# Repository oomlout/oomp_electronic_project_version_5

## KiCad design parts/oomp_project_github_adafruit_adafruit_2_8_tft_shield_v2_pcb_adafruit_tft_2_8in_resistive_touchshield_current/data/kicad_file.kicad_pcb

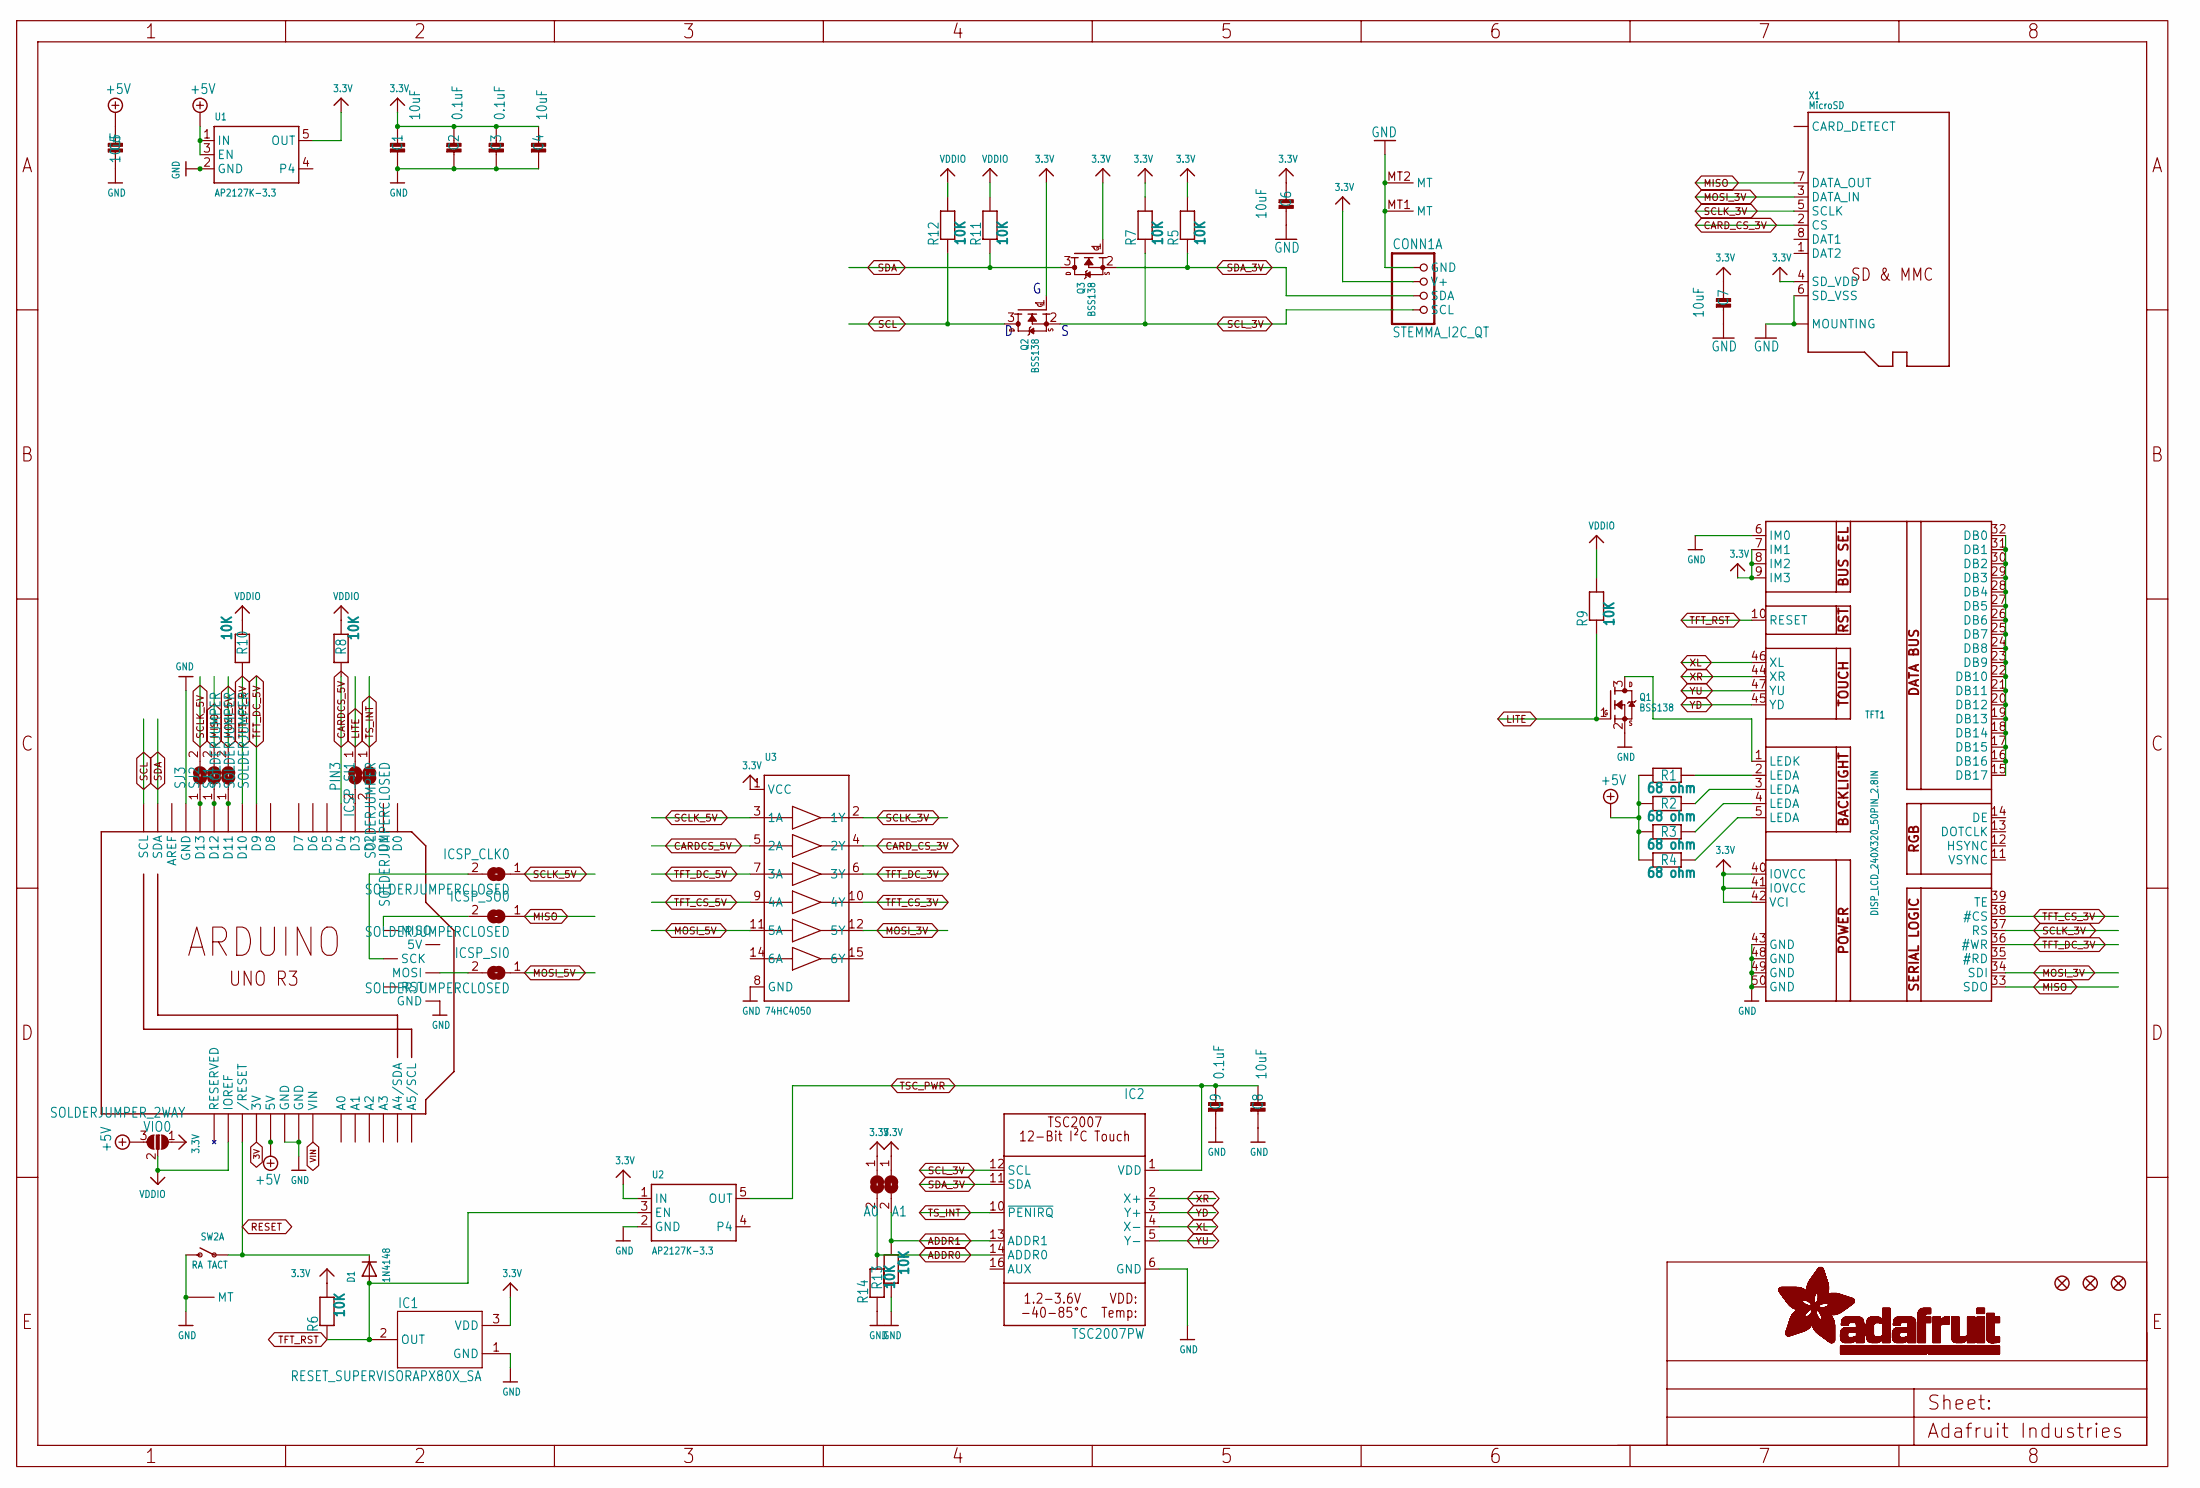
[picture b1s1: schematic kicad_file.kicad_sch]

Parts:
ARD0: ARDUINO_R3_ICSPSMT; ARDUINOR3_ICSP_SMT
C1, C4, C5, C6, C7, C8: 10uF; 0805-NO
C2, C3, C9: 0.1uF; 0603-NO
CONN1: STEMMA_I2C_QT; JST_SH4; LCSC C2845363
D1: 1N4148; SOD-323F
IC1: RESET_SUPERVISORAPX80X_SA; SOT23-WIDE
IC2: TSC2007PW; TSSOP16
ICSP_CLK0: SOLDERJUMPERCLOSED; SOLDERJUMPER_CLOSEDWIRE
ICSP_CLK1: A1; SOLDERJUMPER_ARROW_NOPASTE
ICSP_CLK2: A0; SOLDERJUMPER_ARROW_NOPASTE
ICSP_SI0, ICSP_SI1: SOLDERJUMPERCLOSED; SOLDERJUMPER_CLOSEDWIRE
ICSP_SO0: SOLDERJUMPERCLOSED; SOLDERJUMPER_CLOSEDWIRE
PIN3: SOLDERJUMPER; SOLDERJUMPER_ARROW_NOPASTE
Q1, Q2, Q3: BSS138; SOT23-WIDE
R1, R2, R3, R4: 68 ohm; 0603-NO
R5, R6, R7, R8, R9, R10, R11, R12, R13, R14: 10K; 0603-NO
SJ1, SJ2, SJ3: SOLDERJUMPER; SOLDERJUMPER_ARROW_NOPASTE
SW2: RA TACT; SPST_TACTILE_RA; LCSC C778159
TFT1: DISP_LCD_240X320_50PIN_2.8IN; TFT_2.83IN_240X320_50PIN
U1, U2: AP2127K-3.3; SOT23-5; JLC_ROTATION 270
U3: 74HC4050; SOIC16
U$10, U$11, U$19: FIDUCIAL_1MM
VIO0: SOLDERJUMPER_2WAY; SOLDERJUMPER_2WAY_OPEN_NOPASTE
X1: MicroSD; MICROSD; JLC_ROTATION 90

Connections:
3.3V: C1.1, C2.1, C3.1, C4.1, C6.1, C7.1, CONN1.2 (V+), IC1.3 (VDD), ICSP_CLK1.1, ICSP_CLK2.1, Q2.1 (G), Q3.1 (G), R5.2, R6.2, R7.2, TFT1.7 (IM1), TFT1.8 (IM2), TFT1.9 (IM3), TFT1.40 (IOVCC), TFT1.41 (IOVCC), TFT1.42 (VCI), U1.5 (OUT), U2.1 (IN), U3.1 (VCC), VIO0.1, X1.4 (SD_VDD)
3V: ARD0.3V
+5V: ARD0.5V, C5.1, R1.1, R2.1, R3.1, R4.1, U1.1 (IN), U1.3 (EN), VIO0.3
ADDR0: IC2.14 (ADDR0), ICSP_CLK2.2, R14.2
ADDR1: IC2.13 (ADDR1), ICSP_CLK1.2, R13.2
BACKLITE: ARD0.D3, PIN3.2
CARDCS_5V: ARD0.D4, R8.1, U3.5 (2A)
CARD_CS_3V: U3.4 (2Y), X1.2 (CS)
GND: ARD0.GND, ARD0.GND@1 (GND), ARD0.GND@2 (GND), ARD0.GND@3 (GND), C1.2, C2.2, C3.2, C4.2, C5.2, C6.2, C7.2, C8.2, C9.2, CONN1.1 (GND), CONN1.MT1 (MT), CONN1.MT2 (MT), IC1.1 (GND), IC2.6 (GND), Q1.2 (S), R13.1, R14.1, SW2.2 (S), SW2.MT1 (MT), SW2.MT2 (MT), TFT1.6 (IM0), TFT1.43 (GND), TFT1.48 (GND), TFT1.49 (GND), TFT1.50 (GND), U1.2 (GND), U2.2 (GND), U3.8 (GND), X1.6 (SD_VSS), X1.MT1 (MOUNTING), X1.MT2 (MOUNTING)
LITE: PIN3.1, Q1.1 (G), R9.1
MISO: ICSP_SO0.1, SJ2.2, TFT1.33 (SDO), X1.7 (DATA_OUT)
MOSI_3V: TFT1.34 (SDI), U3.12 (5Y), X1.3 (DATA_IN)
MOSI_5V: ICSP_SI0.1, SJ1.2, U3.11 (5A)
unnamed: Q1.3 (D), TFT1.1 (LEDK)
unnamed: R1.2, TFT1.2 (LEDA)
unnamed: R2.2, TFT1.3 (LEDA)
unnamed: R3.2, TFT1.4 (LEDA)
unnamed: ARD0.MOSI, ICSP_SI0.2
unnamed: ARD0.D2, ICSP_SI1.2
unnamed: TFT1.15 (DB17), TFT1.16 (DB16), TFT1.17 (DB15), TFT1.18 (DB14), TFT1.19 (DB13), TFT1.20 (DB12), TFT1.21 (DB11), TFT1.22 (DB10), TFT1.23 (DB9), TFT1.24 (DB8), TFT1.25 (DB7), TFT1.26 (DB6), TFT1.27 (DB5), TFT1.28 (DB4), TFT1.29 (DB3), TFT1.30 (DB2), TFT1.31 (DB1), TFT1.32 (DB0)
unnamed: R4.2, TFT1.5 (LEDA)
unnamed: ARD0.MISO, ICSP_SO0.2
unnamed: ARD0.SCK, ICSP_CLK0.2
unnamed: ARD0.D13, SJ3.1
unnamed: ARD0.D12, SJ2.1
unnamed: ARD0.D11, SJ1.1
RESET: ARD0.RESET (/RESET), D1.C, SW2.1
SCL: ARD0.SCL, Q2.3 (D), R12.1
SCLK_3V: TFT1.37 (RS), U3.2 (1Y), X1.5 (SCLK)
SCLK_5V: ICSP_CLK0.1, SJ3.2, U3.3 (1A)
SCL_3V: CONN1.4 (SCL), IC2.12 (SCL), Q2.2 (S), R7.1
SDA: ARD0.SDA, Q3.3 (D), R11.1
SDA_3V: CONN1.3 (SDA), IC2.11 (SDA), Q3.2 (S), R5.1
TFT_CS_3V: TFT1.38 (#CS), U3.10 (4Y)
TFT_CS_5V: ARD0.D10, R10.1, U3.9 (4A)
TFT_DC_3V: TFT1.36 (#WR), U3.6 (3Y)
TFT_DC_5V: ARD0.D9, U3.7 (3A)
TFT_RST: D1.A, IC1.2 (OUT), R6.1, TFT1.10 (RESET), U2.3 (EN)
TSC_PWR: C8.1, C9.1, IC2.1 (VDD), U2.5 (OUT)
TS_INT: IC2.10 (~PENIRQ), ICSP_SI1.1
VDDIO: ARD0.IOREF, R8.2, R9.2, R10.2, R11.2, R12.2, VIO0.2
VIN: ARD0.VIN
XL: IC2.4 (X-), TFT1.46 (XL)
XR: IC2.2 (X+), TFT1.44 (XR)
YD: IC2.3 (Y+), TFT1.45 (YD)
YU: IC2.5 (Y-), TFT1.47 (YU)

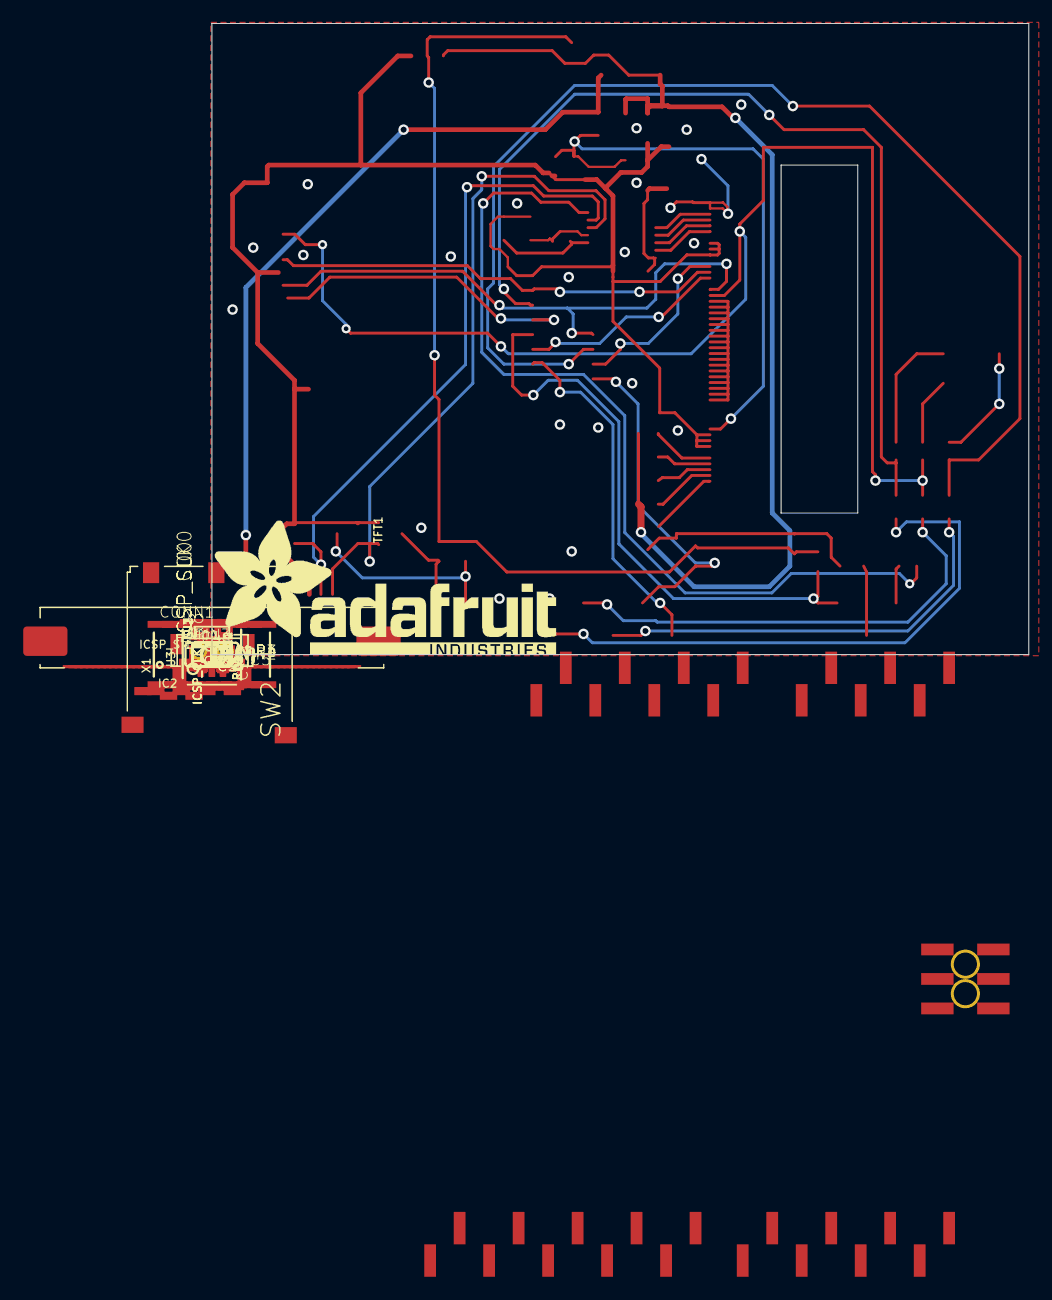
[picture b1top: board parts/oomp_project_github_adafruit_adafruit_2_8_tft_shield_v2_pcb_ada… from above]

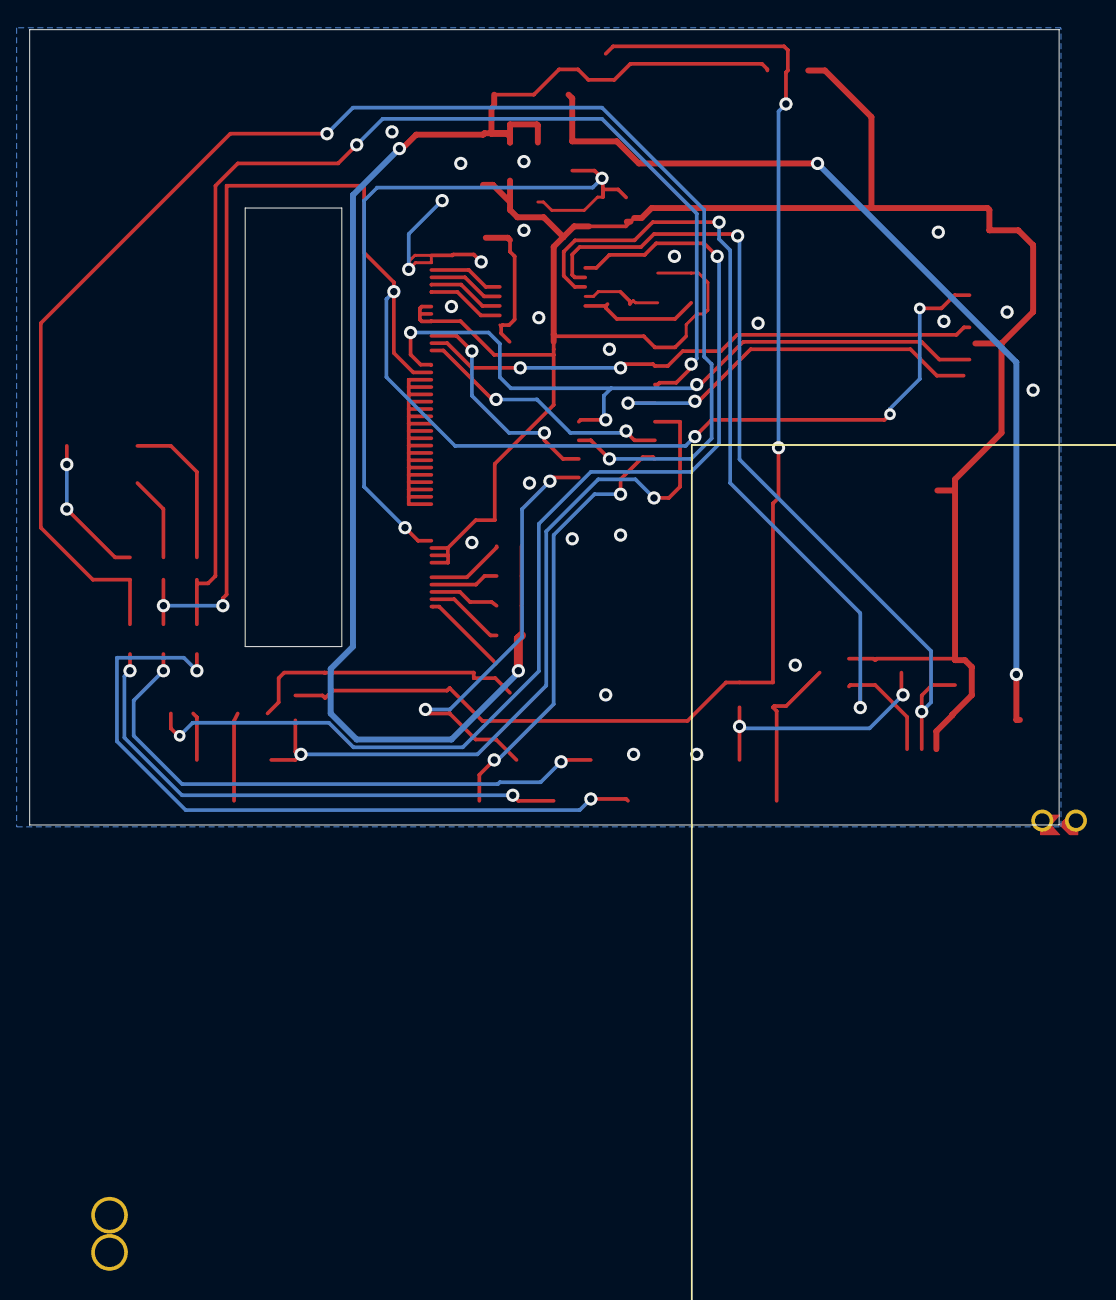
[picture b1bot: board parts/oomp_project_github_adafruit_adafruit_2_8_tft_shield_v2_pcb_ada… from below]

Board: 16 copper layers, 70.4 x 54.4 mm, 76 parts (2 on the bottom side), 44 nets.

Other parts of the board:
PLABEL0: PLABEL0
PLABEL1: PLABEL1
PLABEL2: PLABEL2
PLABEL3: PLABEL3
PLABEL4: PLABEL4
PLABEL5: PLABEL5
PLABEL6: PLABEL6
PLABEL7: PLABEL7
PLABEL8: PLABEL8
PLABEL9: PLABEL9
PLABEL10: PLABEL10
PLABEL11: PLABEL11
PLABEL12: PLABEL12
PLABEL13: PLABEL13
PLABEL14: PLABEL14
PLABEL15: PLABEL15
PLABEL16: PLABEL16
PLABEL17: PLABEL17
PLABEL18: PLABEL18
PLABEL19: PLABEL19
PLABEL20: PLABEL20
PLABEL21: PLABEL21
PLABEL22: PLABEL22
U$3: PCBFEAT-REV-040
U$20: ADAFRUIT_TEXT_30MM

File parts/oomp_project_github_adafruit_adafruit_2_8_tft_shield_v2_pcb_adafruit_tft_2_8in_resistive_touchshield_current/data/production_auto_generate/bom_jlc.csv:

Comment,Designator,Footprint,LCSC Part #
,U$20,Adafruit TFT 2.8in Resistive Touchshield rev E-import-fps:ADAFRUIT_TEXT_30MM,
,U$3,Adafruit TFT 2.8in Resistive Touchshield rev E-import-fps:PCBFEAT-REV-040,
,PLABEL0,Adafruit TFT 2.8in Resistive Touchshield rev E-import-fps:PLABEL0,
,PLABEL1,Adafruit TFT 2.8in Resistive Touchshield rev E-import-fps:PLABEL1,
,PLABEL10,Adafruit TFT 2.8in Resistive Touchshield rev E-import-fps:PLABEL10,
,PLABEL11,Adafruit TFT 2.8in Resistive Touchshield rev E-import-fps:PLABEL11,
,PLABEL12,Adafruit TFT 2.8in Resistive Touchshield rev E-import-fps:PLABEL12,
,PLABEL13,Adafruit TFT 2.8in Resistive Touchshield rev E-import-fps:PLABEL13,
,PLABEL14,Adafruit TFT 2.8in Resistive Touchshield rev E-import-fps:PLABEL14,
,PLABEL15,Adafruit TFT 2.8in Resistive Touchshield rev E-import-fps:PLABEL15,
,PLABEL16,Adafruit TFT 2.8in Resistive Touchshield rev E-import-fps:PLABEL16,
,PLABEL17,Adafruit TFT 2.8in Resistive Touchshield rev E-import-fps:PLABEL17,
,PLABEL18,Adafruit TFT 2.8in Resistive Touchshield rev E-import-fps:PLABEL18,
,PLABEL19,Adafruit TFT 2.8in Resistive Touchshield rev E-import-fps:PLABEL19,
,PLABEL2,Adafruit TFT 2.8in Resistive Touchshield rev E-import-fps:PLABEL2,
,PLABEL20,Adafruit TFT 2.8in Resistive Touchshield rev E-import-fps:PLABEL20,
,PLABEL21,Adafruit TFT 2.8in Resistive Touchshield rev E-import-fps:PLABEL21,
,PLABEL22,Adafruit TFT 2.8in Resistive Touchshield rev E-import-fps:PLABEL22,
,PLABEL3,Adafruit TFT 2.8in Resistive Touchshield rev E-import-fps:PLABEL3,
,PLABEL4,Adafruit TFT 2.8in Resistive Touchshield rev E-import-fps:PLABEL4,
,PLABEL5,Adafruit TFT 2.8in Resistive Touchshield rev E-import-fps:PLABEL5,
,PLABEL6,Adafruit TFT 2.8in Resistive Touchshield rev E-import-fps:PLABEL6,
,PLABEL7,Adafruit TFT 2.8in Resistive Touchshield rev E-import-fps:PLABEL7,
,PLABEL8,Adafruit TFT 2.8in Resistive Touchshield rev E-import-fps:PLABEL8,
,PLABEL9,Adafruit TFT 2.8in Resistive Touchshield rev E-import-fps:PLABEL9,
,VIO0,Adafruit TFT 2.8in Resistive Touchshield rev E-import-fps:SOLDERJUMPER_2WAY_OPEN_NOPASTE,
,PIN3,Adafruit TFT 2.8in Resistive Touchshield rev E-import-fps:SOLDERJUMPER_ARROW_NOPASTE,
,"ICSP_CLK0,ICSP_SI0,ICSP_SI1,ICSP_SO0",Adafruit TFT 2.8in Resistive Touchshield rev E-import-fps:SOLDERJUMPER_CLOSEDWIRE,
0.1uF,"C2,C3,C9",Adafruit TFT 2.8in Resistive Touchshield rev E-import-fps:0603-NO,C14663
10K,"R5,R6,R7,R8,R9,R10,R11,R12,R13,R14",Adafruit TFT 2.8in Resistive Touchshield rev E-import-fps:0603-NO,C98220
10uF,"C1,C4,C5,C6,C7,C8",Adafruit TFT 2.8in Resistive Touchshield rev E-import-fps:0805-NO,
1N4148,D1,Adafruit TFT 2.8in Resistive Touchshield rev E-import-fps:SOD-323F,
68 ohm,"R1,R2,R3,R4",Adafruit TFT 2.8in Resistive Touchshield rev E-import-fps:0603-NO,C27592
74HC4050,U3,Adafruit TFT 2.8in Resistive Touchshield rev E-import-fps:SOIC16,
A0,ICSP_CLK2,Adafruit TFT 2.8in Resistive Touchshield rev E-import-fps:SOLDERJUMPER_ARROW_NOPASTE,
A1,ICSP_CLK1,Adafruit TFT 2.8in Resistive Touchshield rev E-import-fps:SOLDERJUMPER_ARROW_NOPASTE,
AP2127K-3.3,"U1,U2",Adafruit TFT 2.8in Resistive Touchshield rev E-import-fps:SOT23-5,
ARDUINO_R3_ICSPSMT,ARD0,Adafruit TFT 2.8in Resistive Touchshield rev E-import-fps:ARDUINOR3_ICSP_SMT,
BSS138,"Q1,Q2,Q3",Adafruit TFT 2.8in Resistive Touchshield rev E-import-fps:SOT23-WIDE,C52895
DISP_LCD_240X320_50PIN_2.8IN,TFT1,Adafruit TFT 2.8in Resistive Touchshield rev E-import-fps:TFT_2.83IN_240X320_50PIN,
FIDUCIAL_1MM,"U$10,U$11,U$19",Adafruit TFT 2.8in Resistive Touchshield rev E-import-fps:FIDUCIAL_1MM,
MicroSD,X1,Adafruit TFT 2.8in Resistive Touchshield rev E-import-fps:MICROSD,
RA TACT,SW2,Adafruit TFT 2.8in Resistive Touchshield rev E-import-fps:SPST_TACTILE_RA,
RESET_SUPERVISORAPX80X_SA,IC1,Adafruit TFT 2.8in Resistive Touchshield rev E-import-fps:SOT23-WIDE,
STEMMA_I2C_QT,CONN1,Adafruit TFT 2.8in Resistive Touchshield rev E-import-fps:JST_SH4,C160404
TSC2007PW,IC2,Adafruit TFT 2.8in Resistive Touchshield rev E-import-fps:TSSOP16,

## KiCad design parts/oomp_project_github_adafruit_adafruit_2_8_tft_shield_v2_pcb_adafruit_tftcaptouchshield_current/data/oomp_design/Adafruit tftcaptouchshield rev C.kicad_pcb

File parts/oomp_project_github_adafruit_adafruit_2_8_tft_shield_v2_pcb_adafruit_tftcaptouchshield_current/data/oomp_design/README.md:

# OOMP KiCad design copy

Open `Adafruit tftcaptouchshield rev C.kicad_pro` (or the `.kicad_pcb` / `.kicad_sch`) in KiCad. Local OOMP libraries are under `libraries/`. Original inputs are preserved in [../original/](../original/).

Only verified unchanged installed KiCad defaults were renamed. Modified, custom, unmatched and unavailable items remain unchanged. Soldering variants are never swapped during conversion. Existing pad coordinates, nets and UUIDs are preserved.

See [conversion_report.yaml](conversion_report.yaml) for every conversion and skip. Copy this directory before editing; regeneration refuses to overwrite edited design files.

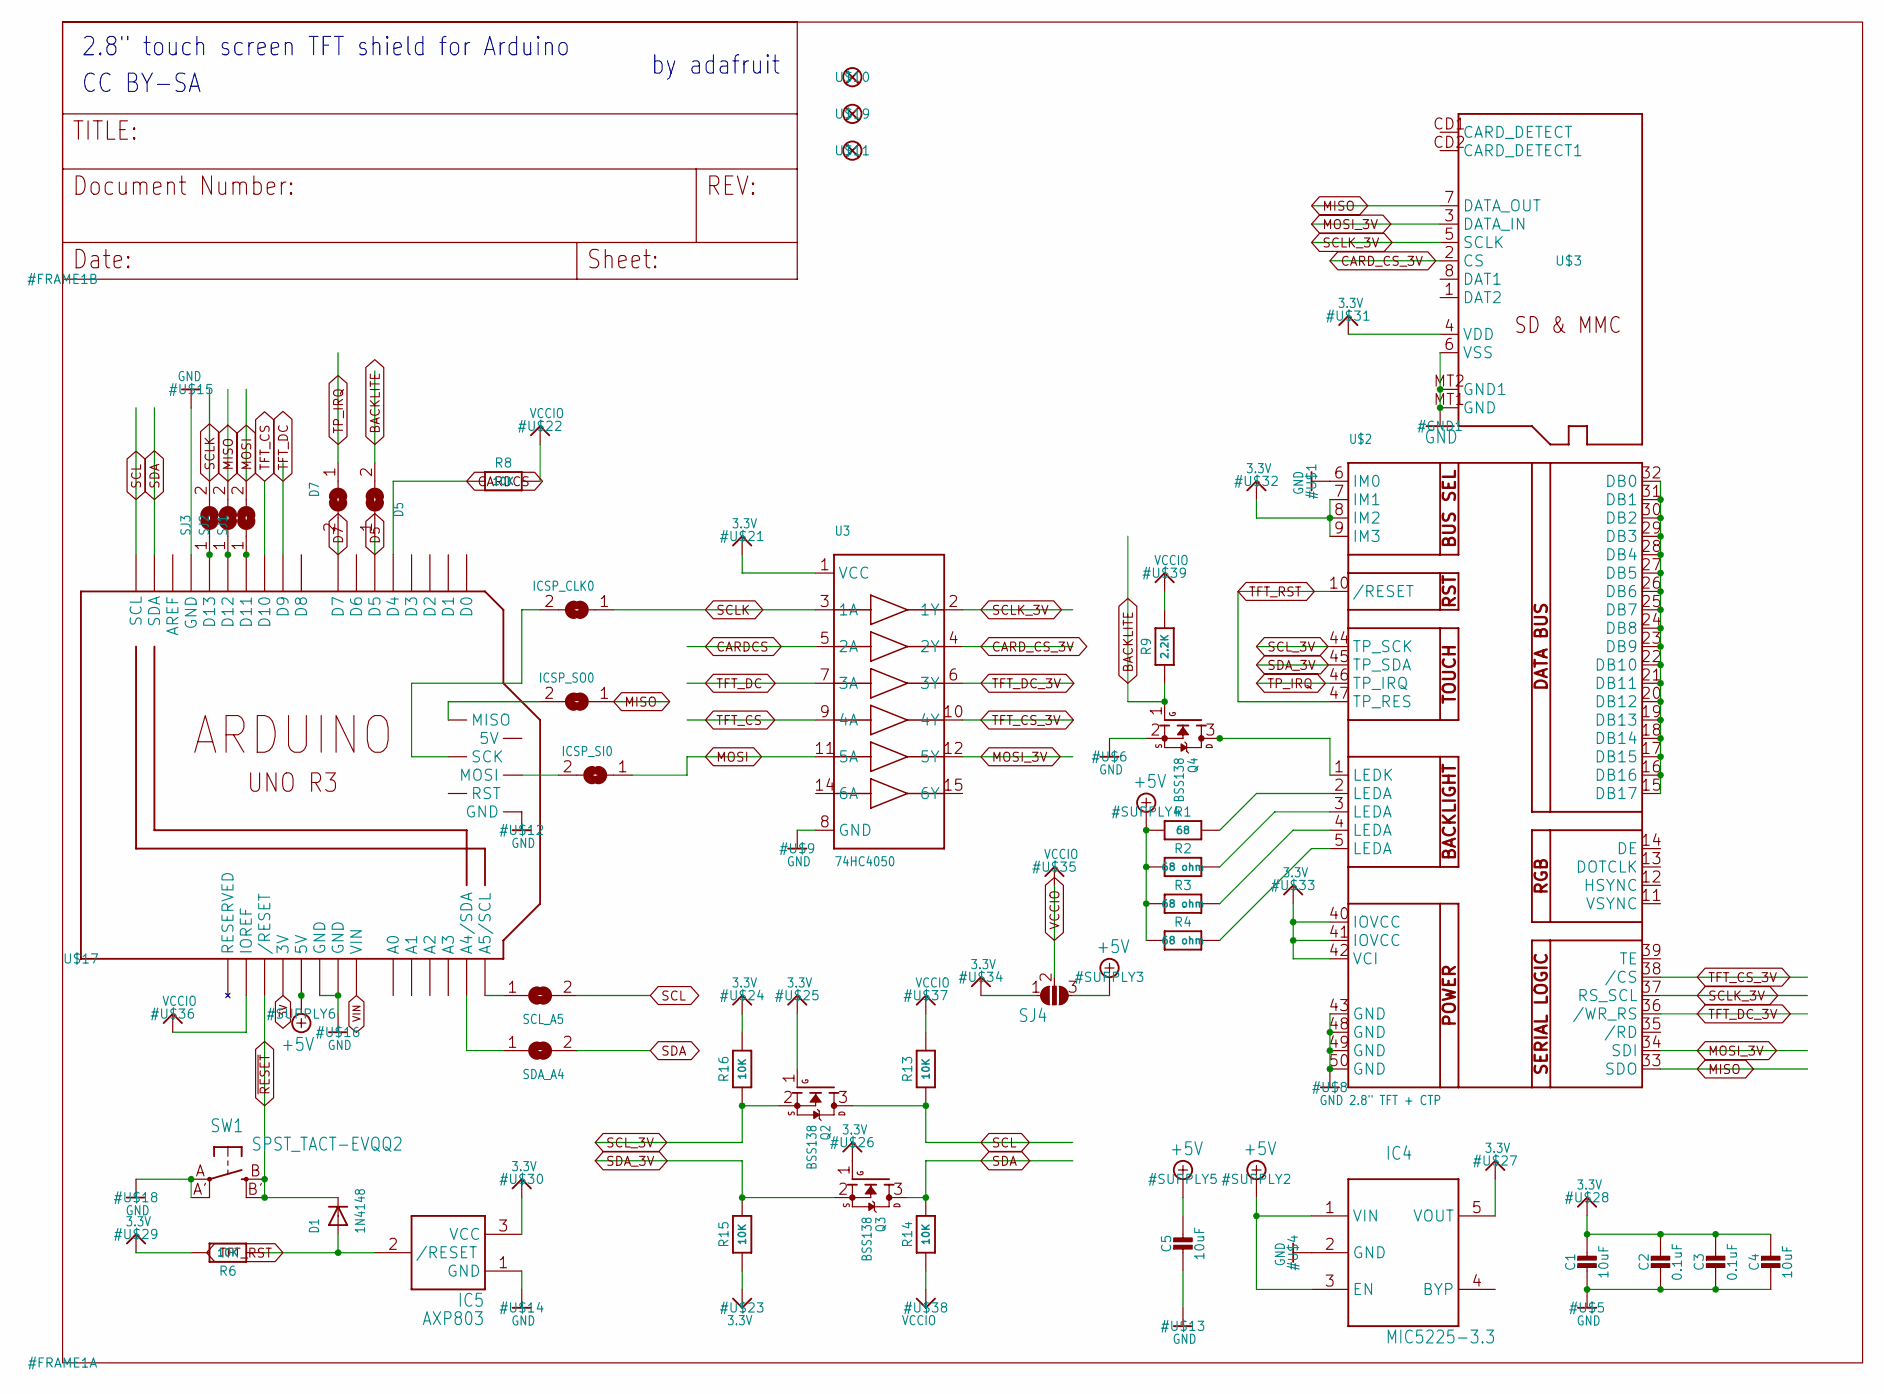
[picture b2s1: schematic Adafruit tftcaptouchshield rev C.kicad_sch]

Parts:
C1, C4, C5: 10uF; 0805-NO
C2, C3: 0.1uF; 0805-NO
D1: 1N4148; SOD-323F
D5, D7: SOLDERJUMPER; SOLDERJUMPER_ARROW_NOPASTE
IC4: MIC5225-3.3; SOT23-5L
IC5: AXP803; SOT23
ICSP_CLK0: SOLDERJUMPERCLOSED; SOLDERJUMPER_CLOSEDWIRE
ICSP_SI0: SOLDERJUMPERCLOSED; SOLDERJUMPER_CLOSEDWIRE
ICSP_SO0: SOLDERJUMPERCLOSED; SOLDERJUMPER_CLOSEDWIRE
Q2, Q3, Q4: BSS138; SOT23-WIDE
R1: 68; 0805-NO
R2, R3, R4: 68 ohm; 0805-NO
R6, R8, R13, R14, R15, R16: 10K; 0805-NO
R9: 2.2K; 0805-NO
SCL_A5: SOLDERJUMPERREFLOW_NOPASTE; SOLDERJUMPER_REFLOW_NOPASTE
SDA_A4: SOLDERJUMPERREFLOW_NOPASTE; SOLDERJUMPER_REFLOW_NOPASTE
SJ1, SJ2, SJ3: SOLDERJUMPER; SOLDERJUMPER_ARROW_NOPASTE
SJ4: SOLDERJUMPER_2WAY; SOLDERJUMPER_2WAY_OPEN_NOPASTE
SW1: SPST_TACT-EVQQ2; EVQ-Q2
U3: 74HC4050; SOIC16
U$2: 2.8" TFT + CTP; TFT_2.83IN_240X320_50PIN
U$3: MICROSD
U$10, U$11, U$19: FIDUCIAL_1MM
U$17: ARDUINO_R3_ICSPSMT; ARDUINOR3_ICSP_SMT

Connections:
3.3V: C1.1, C2.1, C3.1, C4.1, IC4.5 (VOUT), IC5.3 (VCC), Q2.1 (G), Q3.1 (G), R6.2, R15.1, R16.2, SJ4.1, U3.1 (VCC), U$2.7 (IM1), U$2.8 (IM2), U$2.9 (IM3), U$2.40 (IOVCC), U$2.41 (IOVCC), U$2.42 (VCI), U$3.4 (VDD)
3V: U$17.3V
+5V: C5.1, IC4.1 (VIN), IC4.3 (EN), R1.1, R2.1, R3.1, R4.1, SJ4.3, U$17.5V
BACKLITE: D5.2, Q4.1 (G), R9.1
CARDCS: R8.1, U3.5 (2A), U$17.D4
CARD_CS_3V: U3.4 (2Y), U$3.2 (CS)
D5: D5.1, U$17.D5
D7: D7.2, U$17.D7
GND: C1.2, C2.2, C3.2, C4.2, C5.2, IC4.2 (GND), IC5.1 (GND), Q4.2 (S), SW1.A, SW1.A' (P1), U3.8 (GND), U$2.6 (IM0), U$2.43 (GND), U$2.48 (GND), U$2.49 (GND), U$2.50 (GND), U$3.6 (VSS), U$3.MT1 (GND), U$3.MT2 (GND1), U$17.GND, U$17.GND@1 (GND), U$17.GND@2 (GND), U$17.GND@3 (GND)
MISO: ICSP_SO0.1, SJ2.2, U$2.33 (SDO), U$3.7 (DATA_OUT)
MOSI: ICSP_SI0.1, SJ1.2, U3.11 (5A)
MOSI_3V: U3.12 (5Y), U$2.34 (SDI), U$3.3 (DATA_IN)
unnamed: Q4.3 (D), U$2.1 (LEDK)
unnamed: R1.2, U$2.2 (LEDA)
unnamed: R2.2, U$2.3 (LEDA)
unnamed: R3.2, U$2.4 (LEDA)
unnamed: ICSP_SI0.2, U$17.MOSI
unnamed: U$2.15 (DB17), U$2.16 (DB16), U$2.17 (DB15), U$2.18 (DB14), U$2.19 (DB13), U$2.20 (DB12), U$2.21 (DB11), U$2.22 (DB10), U$2.23 (DB9), U$2.24 (DB8), U$2.25 (DB7), U$2.26 (DB6), U$2.27 (DB5), U$2.28 (DB4), U$2.29 (DB3), U$2.30 (DB2), U$2.31 (DB1), U$2.32 (DB0)
unnamed: R4.2, U$2.5 (LEDA)
unnamed: ICSP_SO0.2, U$17.MISO
unnamed: ICSP_CLK0.2, U$17.SCK
unnamed: SJ3.1, U$17.D13
unnamed: SJ2.1, U$17.D12
unnamed: SJ1.1, U$17.D11
unnamed: SDA_A4.1, U$17.A4 (A4/SDA)
unnamed: SCL_A5.1, U$17.A5 (A5/SCL)
SCL: Q2.3 (D), R13.1, SCL_A5.2, U$17.SCL
SCLK: ICSP_CLK0.1, SJ3.2, U3.3 (1A)
SCLK_3V: U3.2 (1Y), U$2.37 (RS_SCL), U$3.5 (SCLK)
SCL_3V: Q2.2 (S), R16.1, U$2.44 (TP_SCK)
SDA: Q3.3 (D), R14.2, SDA_A4.2, U$17.SDA
SDA_3V: Q3.2 (S), R15.2, U$2.45 (TP_SDA)
TFT_CS: U3.9 (4A), U$17.D10
TFT_CS_3V: U3.10 (4Y), U$2.38 (/CS)
TFT_DC: U3.7 (3A), U$17.D9
TFT_DC_3V: U3.6 (3Y), U$2.36 (/WR_RS)
TFT_RST: D1.A, IC5.2 (/RESET), R6.1, U$2.10 (/RESET), U$2.47 (TP_RES)
TP_IRQ: D7.1, U$2.46 (TP_IRQ)
VCCIO: R8.2, R9.2, R13.2, R14.1, SJ4.2, U$17.IOREF
VIN: U$17.VIN
~RESET: D1.C, SW1.B (S), SW1.B' (S1), U$17.RESET (/RESET)

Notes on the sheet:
by adafruit~{}
CC BY-SA
2.8" touch screen TFT shield for Arduino

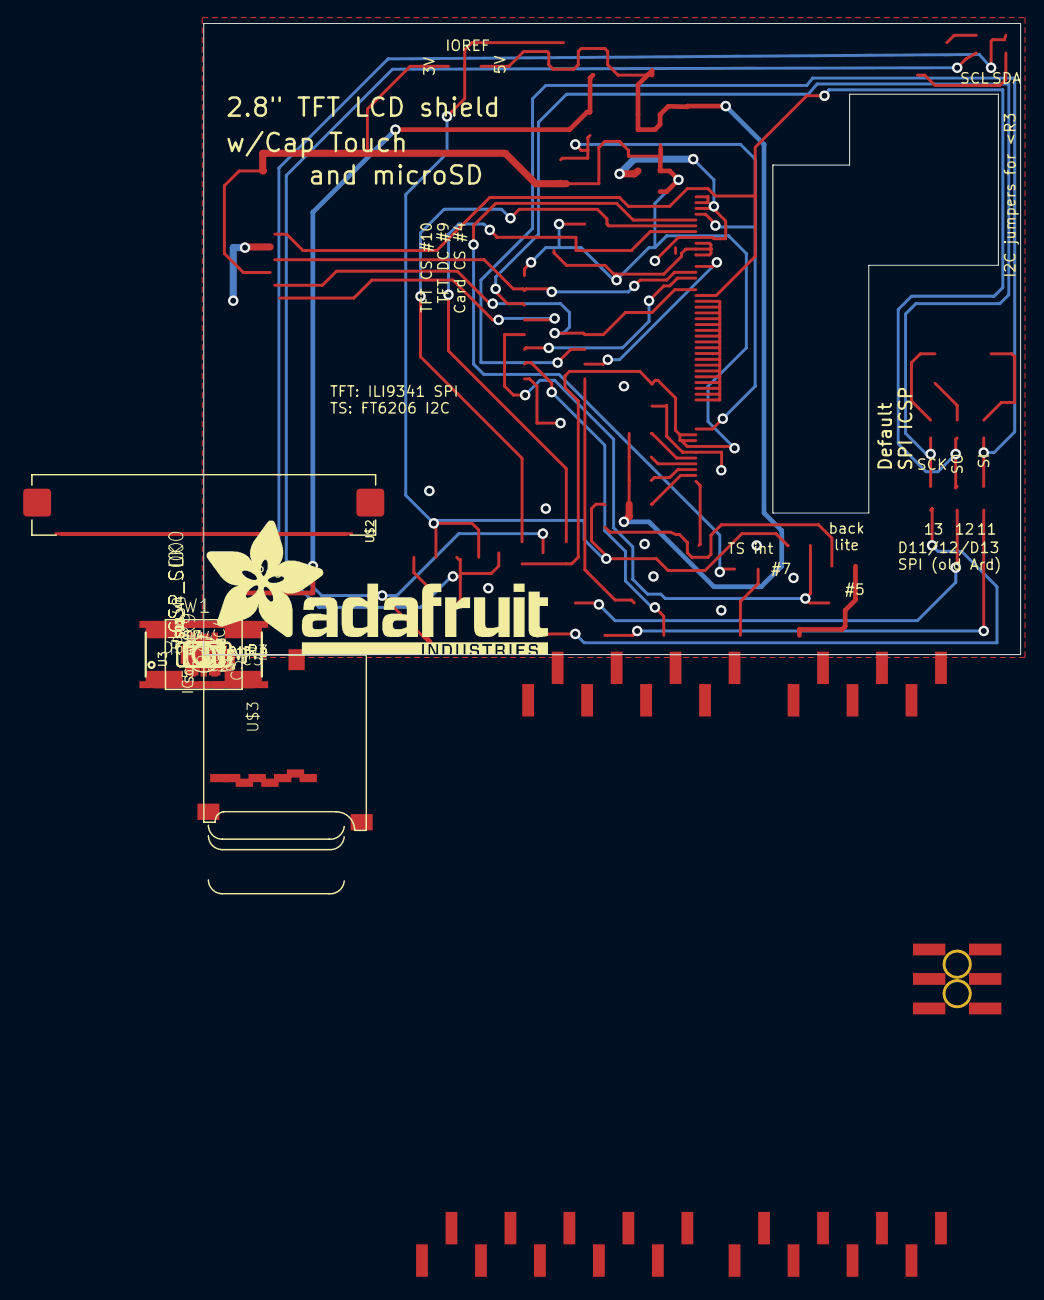
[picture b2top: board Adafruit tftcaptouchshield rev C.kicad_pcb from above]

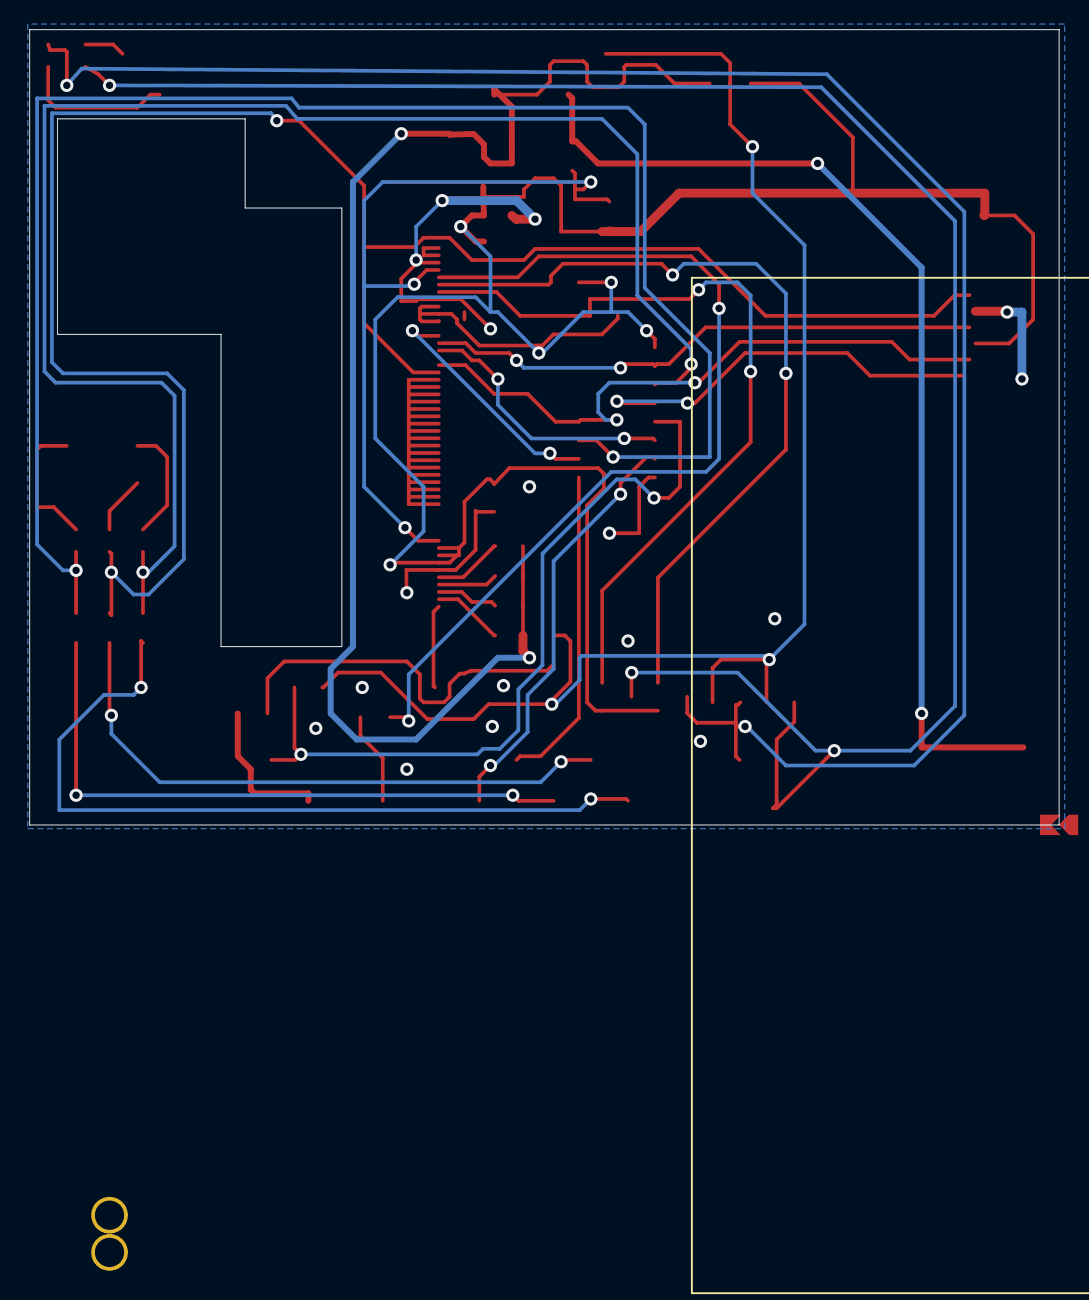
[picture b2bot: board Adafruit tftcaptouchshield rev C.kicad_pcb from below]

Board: 16 copper layers, 70.4 x 54.4 mm, 43 parts (2 on the bottom side), 39 nets.

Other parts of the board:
U$7: PCBFEAT-REV-040
U$20: ADAFRUIT_TEXT_30MM

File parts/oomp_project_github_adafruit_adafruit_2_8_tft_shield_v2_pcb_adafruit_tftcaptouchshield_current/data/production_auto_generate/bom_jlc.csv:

Comment,Designator,Footprint,LCSC Part #
,U$20,Adafruit tftcaptouchshield rev C-import-fps:ADAFRUIT_TEXT_30MM,
,U$7,Adafruit tftcaptouchshield rev C-import-fps:PCBFEAT-REV-040,
,"D5,D7",Adafruit tftcaptouchshield rev C-import-fps:SOLDERJUMPER_ARROW_NOPASTE,
,"ICSP_CLK0,ICSP_SI0,ICSP_SO0",Adafruit tftcaptouchshield rev C-import-fps:SOLDERJUMPER_CLOSEDWIRE,
,"SCL_A5,SDA_A4",Adafruit tftcaptouchshield rev C-import-fps:SOLDERJUMPER_REFLOW_NOPASTE,
0.1uF,"C2,C3",Adafruit tftcaptouchshield rev C-import-fps:0805-NO,
10K,"R6,R8,R13,R14,R15,R16",Adafruit tftcaptouchshield rev C-import-fps:0805-NO,C17414
10uF,"C1,C4,C5",Adafruit tftcaptouchshield rev C-import-fps:0805-NO,
1N4148,D1,Adafruit tftcaptouchshield rev C-import-fps:SOD-323F,
2.2K,R9,Adafruit tftcaptouchshield rev C-import-fps:0805-NO,C17520
"2.8"" TFT + CTP",U$2,Adafruit tftcaptouchshield rev C-import-fps:TFT_2.83IN_240X320_50PIN,
68,R1,Adafruit tftcaptouchshield rev C-import-fps:0805-NO,C2933487
68 ohm,"R2,R3,R4",Adafruit tftcaptouchshield rev C-import-fps:0805-NO,C2933487
74HC4050,U3,Adafruit tftcaptouchshield rev C-import-fps:SOIC16,
ARDUINO_R3_ICSPSMT,U$17,Adafruit tftcaptouchshield rev C-import-fps:ARDUINOR3_ICSP_SMT,
AXP803,IC5,Adafruit tftcaptouchshield rev C-import-fps:SOT23,
BSS138,"Q2,Q3,Q4",Adafruit tftcaptouchshield rev C-import-fps:SOT23-WIDE,C52895
FIDUCIAL_1MM,"U$10,U$11,U$19",Adafruit tftcaptouchshield rev C-import-fps:FIDUCIAL_1MM,
MIC5225-3.3,IC4,Adafruit tftcaptouchshield rev C-import-fps:SOT23-5L,
MICROSD,U$3,Adafruit tftcaptouchshield rev C-import-fps:MICROSD,
SPST_TACT-EVQQ2,SW1,Adafruit tftcaptouchshield rev C-import-fps:EVQ-Q2,
